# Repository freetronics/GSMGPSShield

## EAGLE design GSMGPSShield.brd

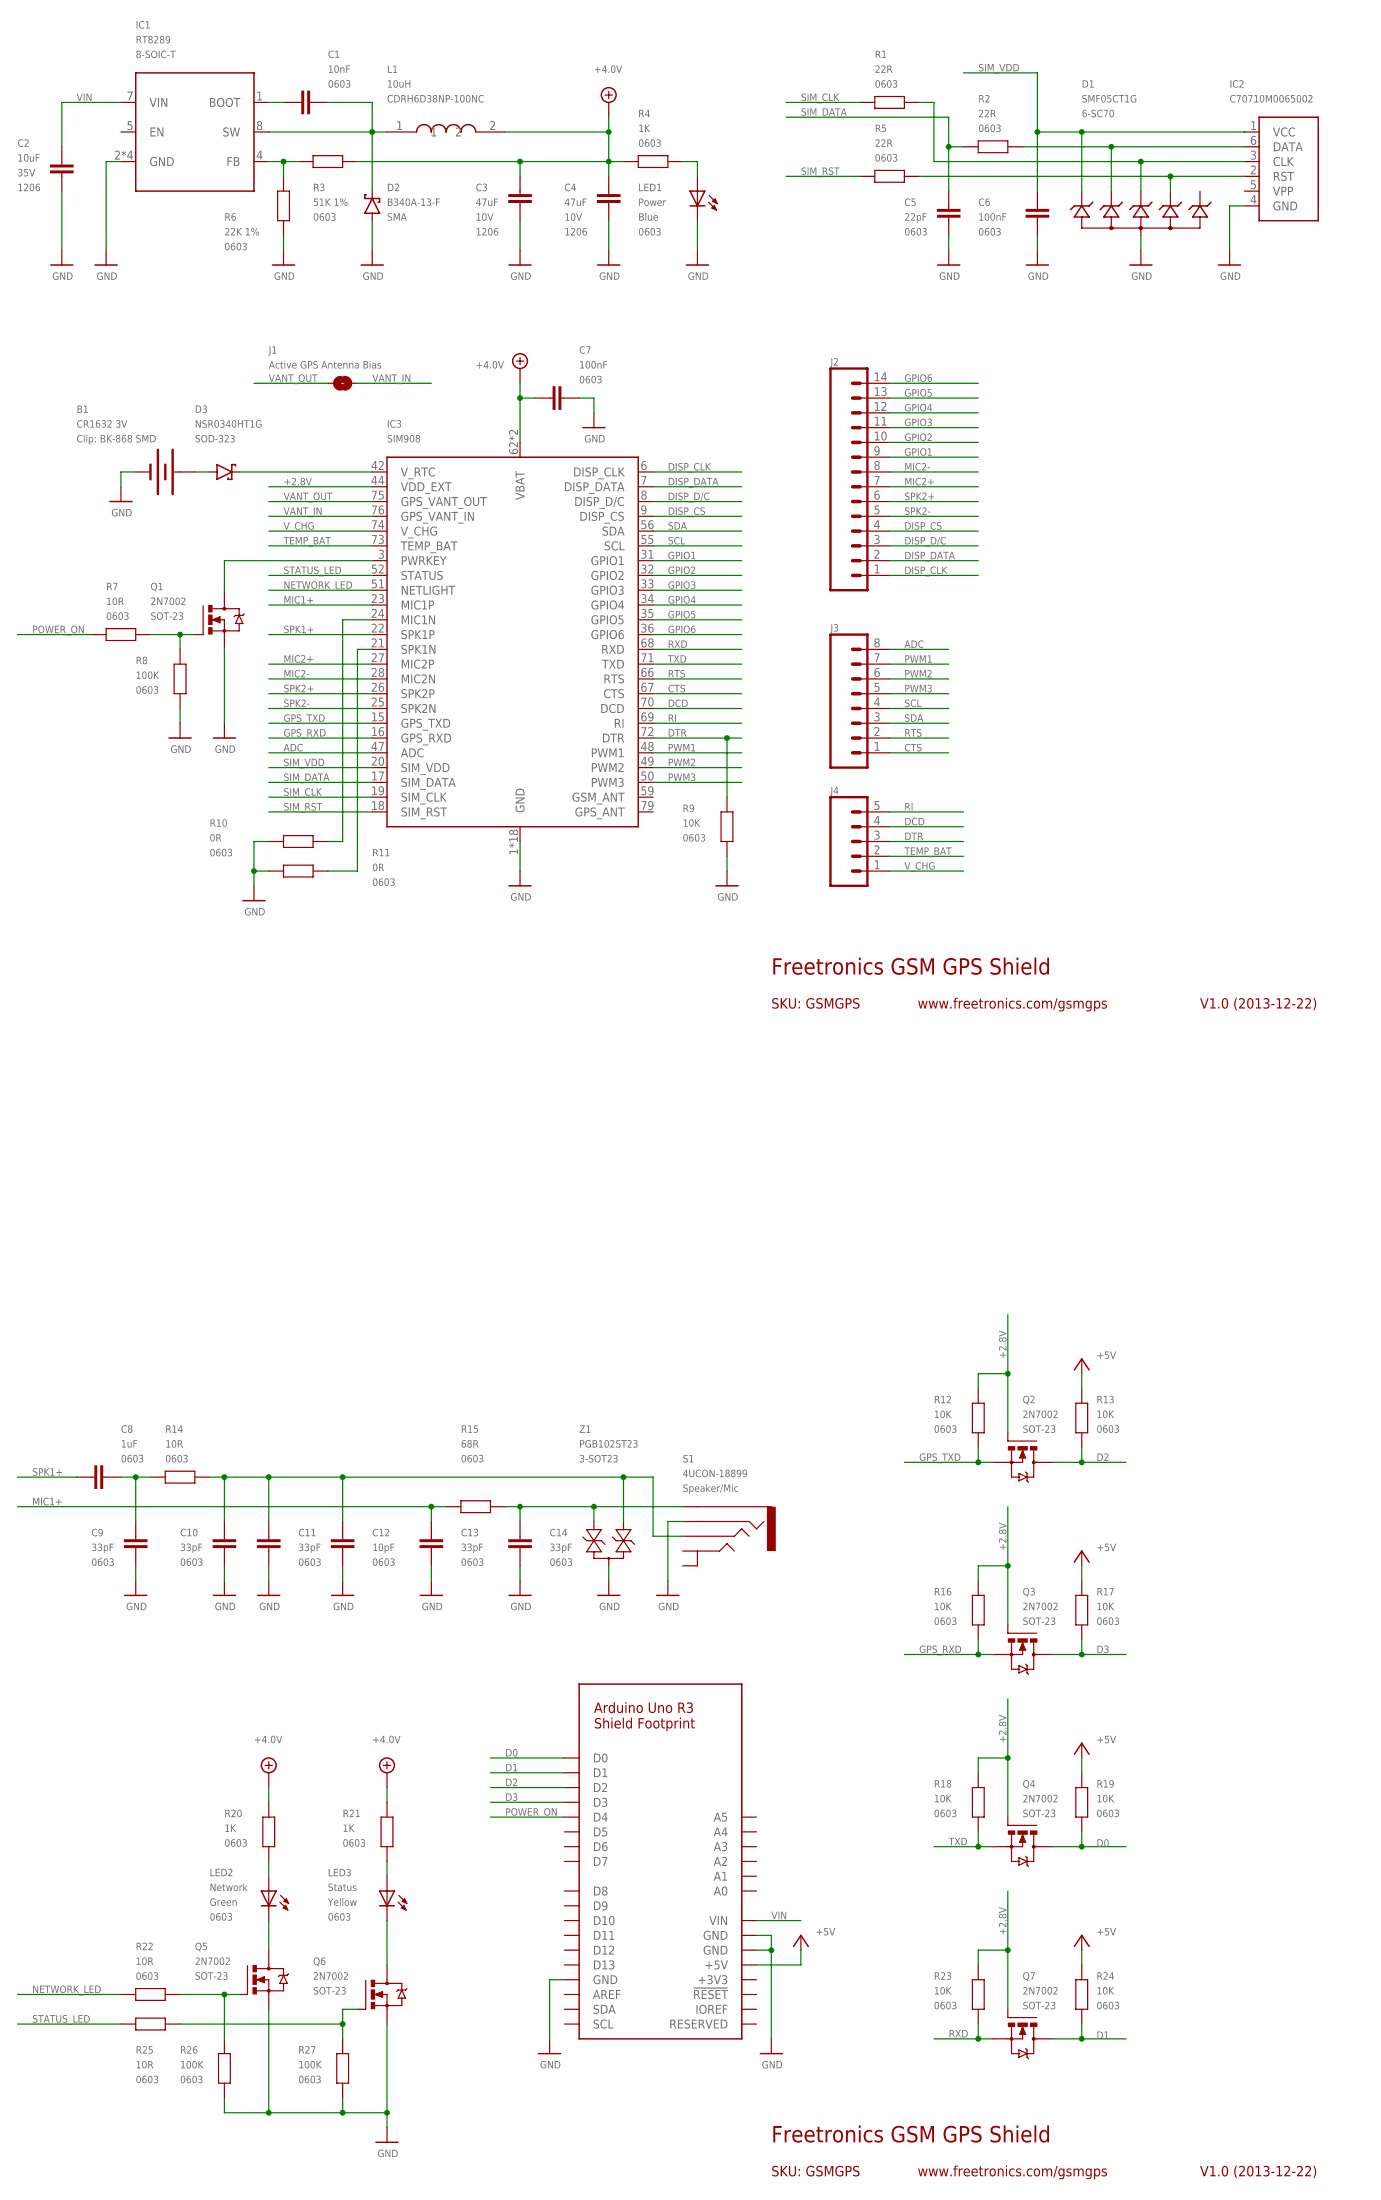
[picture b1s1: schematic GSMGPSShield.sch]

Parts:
B1: CR1632 3V; BATCON_16MM
C1: 10nF; 0603
C2: 10uF; C1206; VOLTAGE 35V
C3, C4: 47uF; C1206; VOLTAGE 10V
C5: 22pF; 0603
C6, C7: 100nF; 0603
C8: 1uF; 0603
C9, C10, C11, C13, C14: 33pF; 0603
C12: 10pF; 0603
D1: SMF05CT1G; SC70-6
D2: B340A-13-F; SMA
D3: NSR0340HT1G; SOD-323
IC1: RT8289; SO08T
IC2: C70710M0065002
IC3: SIM908
J1: Active GPS Antenna Bias; SJ
J2: M14; 1X14
J3: M08STD; 1X08
J4: M05PTH; 1X05
J5: ARDUINO-SHIELD_R3_NOISP
L1: 10uH; CDRH
LED1: Power; LED-0603
LED2: Network; LED-0603
LED3: Status; LED-0603
Q1, Q2, Q3, Q4, Q5, Q6, Q7: 2N7002; SOT23-3
R1, R2, R5: 22R; 0603
R3: 51K 1%; 0603
R4, R20, R21: 1K; 0603
R6: 22K 1%; 0603
R7, R14, R22, R25: 10R; 0603
R8, R26, R27: 100K; 0603
R9, R12, R13, R16, R17, R18, R19, R23, R24: 10K; 0603
R10, R11: 0R; 0603
R15: 68R; 0603
S1: 4UCON-18899
Z1: PGB102ST23; SOT23-3

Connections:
+2.8V: IC3.44 (VDD_EXT), Q2.1 (G), Q3.1 (G), Q4.1 (G), Q7.1 (G), R12.1, R16.1, R18.1, R23.1
+3V3: J5.3V3 (+3V3)
+4.0V: C3.1, C4.1, C7.2, IC3.62 (VBAT), IC3.63 (VBAT), L1.2, R3.1, R4.1, R20.1, R21.1
+5V: J5.+5V, R13.1, R17.1, R19.1, R24.1
ADC: IC3.47 (ADC), J3.8
CTS: IC3.67 (CTS), J3.1
D0: J5.D0, Q4.3 (D), R19.2
D1: J5.D1, Q7.3 (D), R24.2
D2: J5.D2, Q2.3 (D), R13.2
D3: J5.D3, Q3.3 (D), R17.2
DCD: IC3.70 (DCD), J4.4
DISP_CLK: IC3.6 (DISP_CLK), J2.1
DISP_CS: IC3.9 (DISP_CS), J2.4
DISP_D/C: IC3.8 (DISP_D/C), J2.3
DISP_DATA: IC3.7 (DISP_DATA), J2.2
DTR: IC3.72 (DTR), J4.3, R9.1
GND: B1.GND (-), C2.2, C3.2, C4.2, C5.1, C6.1, C7.1, C9.1, C10.1, C11.1, C12.1, C13.1, C14.1, D1.2 (A2), D2.A, IC1.2 (GND), IC1.3 (GND), IC1.6 (GND), IC1.PAD (GND), IC2.4 (GND), IC3.1 (GND), IC3.2 (GND), IC3.5 (GND), IC3.10 (GND), IC3.14 (GND), IC3.37 (GND), IC3.40 (GND), IC3.41 (GND), IC3.43 (GND), IC3.57 (GND), IC3.58 (GND), IC3.60 (GND), IC3.61 (GND), IC3.64 (GND), IC3.65 (GND), IC3.77 (GND), IC3.78 (GND), IC3.80 (GND), J5.GND, J5.GND@0 (GND), J5.GND@1 (GND), LED1.C, Q1.2 (S), Q5.2 (S), Q6.2 (S), R6.1, R8.1, R9.2, R10.2, R11.2, R26.1, R27.1, S1.4, Z1.3
GPIO1: IC3.31 (GPIO1), J2.9
GPIO2: IC3.32 (GPIO2), J2.10
GPIO3: IC3.33 (GPIO3), J2.11
GPIO4: IC3.34 (GPIO4), J2.12
GPIO5: IC3.35 (GPIO5), J2.13
GPIO6: IC3.36 (GPIO6), J2.14
GPS_RXD: IC3.16 (GPS_RXD), Q3.2 (S), R16.2
GPS_TXD: IC3.15 (GPS_TXD), Q2.2 (S), R12.2
MIC1+: C13.2, IC3.23 (MIC1P), R15.1
MIC2+: IC3.27 (MIC2P), J2.7
MIC2-: IC3.28 (MIC2N), J2.8
unnamed: LED1.A, R4.2
unnamed: LED2.C, Q5.3 (D)
unnamed: LED3.C, Q6.3 (D)
unnamed: Q5.1 (G), R22.1, R26.2
unnamed: Q6.1 (G), R25.1, R27.2
unnamed: D3.K, IC3.42 (V_RTC)
unnamed: IC3.3 (PWRKEY), Q1.3 (D)
unnamed: B1.PWR@1 (+), D3.A
unnamed: IC3.21 (SPK1N), R11.1
unnamed: IC3.24 (MIC1N), R10.1
unnamed: D1.5 (K5), IC2.2 (RST), R5.1
unnamed: D1.4 (K4), IC2.3 (CLK), R1.1
unnamed: D1.3 (K3), IC2.6 (DATA), R2.1
unnamed: C14.2, R15.2, S1.1, Z1.2
unnamed: C10.2, C11.2, C12.2, R14.2, S1.3, Z1.1
unnamed: C8.1, C9.2, R14.1
unnamed: Q1.1 (G), R7.1, R8.2
unnamed: LED3.A, R21.2
unnamed: LED2.A, R20.2
unnamed: C1.1, D2.K, IC1.8 (SW), L1.1
unnamed: IC1.4 (FB), R3.2, R6.2
unnamed: C1.2, IC1.1 (BOOT)
NETWORK_LED: IC3.51 (NETLIGHT), R22.2
POWER_ON: J5.D4, R7.2
PWM1: IC3.48 (PWM1), J3.7
PWM2: IC3.49 (PWM2), J3.6
PWM3: IC3.50 (PWM3), J3.5
RI: IC3.69 (RI), J4.5
RTS: IC3.66 (RTS), J3.2
RXD: IC3.68 (RXD), Q7.2 (S), R23.2
SCL: IC3.55 (SCL), J3.4
SDA: IC3.56 (SDA), J3.3
SIM_CLK: IC3.19 (SIM_CLK), R1.2
SIM_DATA: C5.2, IC3.17 (SIM_DATA), R2.2
SIM_RST: IC3.18 (SIM_RST), R5.2
SIM_VDD: C6.2, D1.1 (K1), IC2.1 (VCC), IC3.20 (SIM_VDD)
SPK1+: C8.2, IC3.22 (SPK1P)
SPK2+: IC3.26 (SPK2P), J2.6
SPK2-: IC3.25 (SPK2N), J2.5
STATUS_LED: IC3.52 (STATUS), R25.2
TEMP_BAT: IC3.73 (TEMP_BAT), J4.2
TXD: IC3.71 (TXD), Q4.2 (S), R18.2
VANT_IN: IC3.76 (GPS_VANT_IN), J1.2
VANT_OUT: IC3.75 (GPS_VANT_OUT), J1.1
VIN: C2.1, IC1.7 (VIN), J5.VIN
V_CHG: IC3.74 (V_CHG), J4.1

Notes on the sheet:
Freetronics GSM GPS Shield
V1.0 (2013-12-22)
www.freetronics.com/gsmgps
SKU: GSMGPS

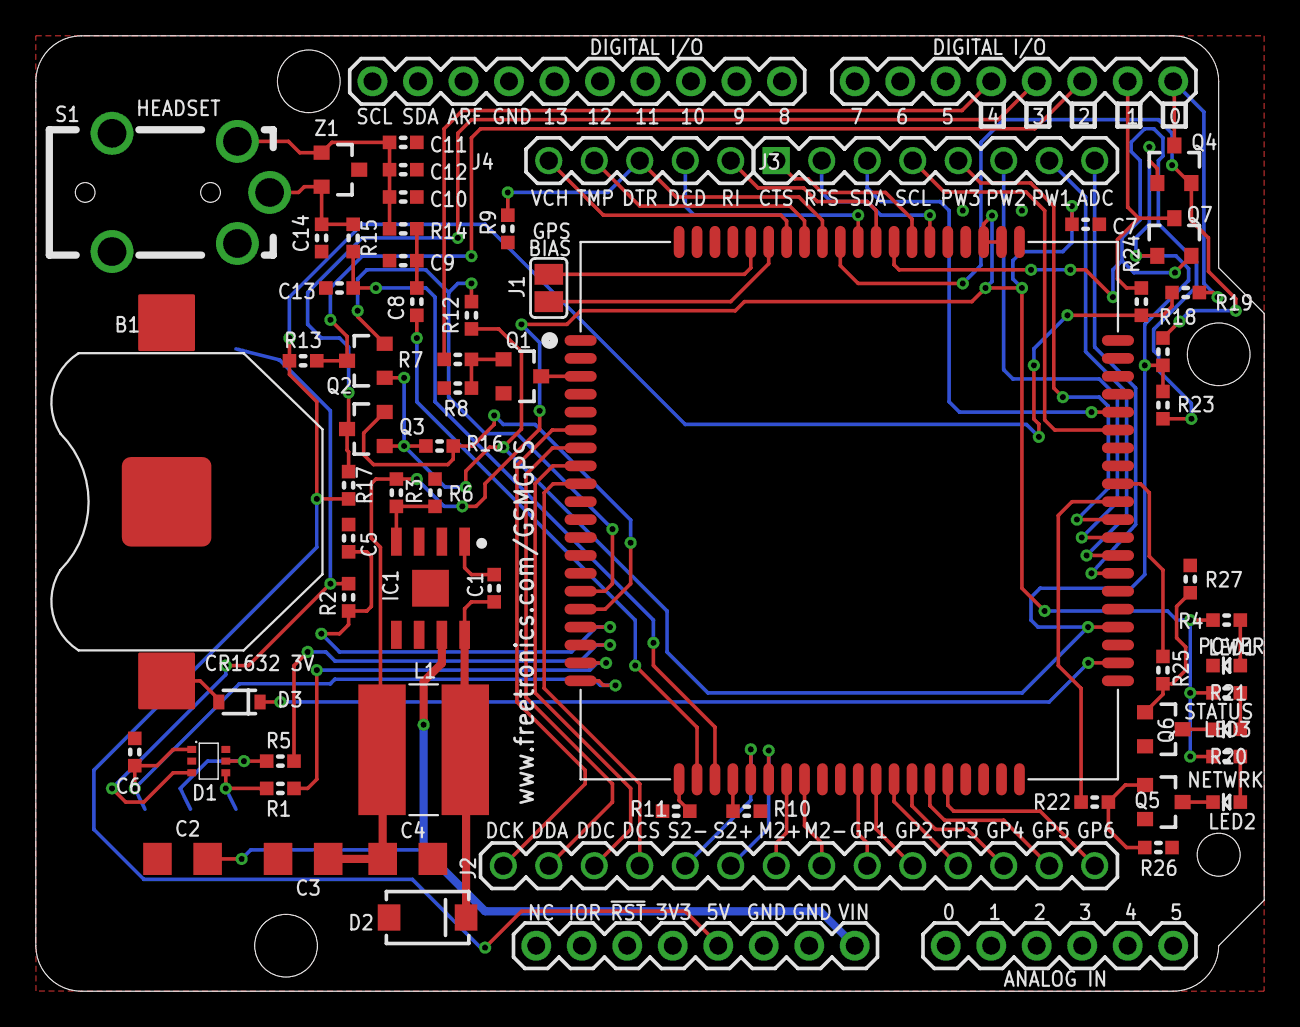
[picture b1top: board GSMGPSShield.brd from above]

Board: 2 copper layers, 68.6 x 53.3 mm, 66 parts (1 on the bottom side), 73 nets.

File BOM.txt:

B1	Memory Protection Devices BK-868 SMD CR1632 coin cell holder (Digi-Key BK-868-ND)
NOTE: A CR1632 3V lithium coin cell also needs to be supplied and mounted in the socket.

S1	4UCON 18899 4-pole audio jack, same as Freetronics ArduPhone
Z1	Littelfuse PGB102ST23WR dual TVS diode, 3-SOT23 package. (Digi-Key F2596CT-ND)

IC3	SIMCom SIM908 GPRS/GPS Module

NOTE: Antenna pigtails with appropriate RF connectors are required to connect to both the GSM and GPS antenna ports on the SIM908 module.

L1	Sumida CDRH6D38NP-100NC 10uH SMD inductor (Digi-Key 308-1541-1-ND) - same footprint as EtherMega inductor

IC1	Richtek RT8289GSP buck converter, 8-SOIC SMD with exposed pad (Digi-Key 1028-1046-1-ND)
IC2	SIM card socket, Amphenol "C707 10M0065 002" 6-pin SIM socket (Digi-Key 361-1020-1-ND)

NOTE: User also needs to supply SIM card, of course.

D1	SMF05CT1G 5-way ESD supressor array, SC70-6 package (Digi-Key SMF05CT1GOSCT-ND)
D2	B340A-13-F schottky diode, SMA package (Digi-Key B340A-FDICT-ND)
D3	NSR0340HT1G schottky diode, SOD323 package (Digi-Key NSR0340HT1GOSCT-ND)

J5	Arduino Shield Headers (2 x 8-pin, 1 x 10-pin, 1 x 6-pin) - placement optional
J2	14-pin 0.1" pin header (NOT PLACED)
J3	8-pin 0.1" pin header (NOT PLACED)

LED1	Blue LED, 0603 SMD
LED2	Green LED, 0603 SMD
LED3	Yellow LED, 0603 SMD

Q1	2N7002 3-SOT23
Q2	2N7002 3-SOT23
Q3	2N7002 3-SOT23
Q4	2N7002 3-SOT23
Q5	2N7002 3-SOT23
Q6	2N7002 3-SOT23
Q7	2N7002 3-SOT23

R1	22R 0603 SMD
R2	22R 0603 SMD
R3	51k 1% 0603 SMD
R4	1k 0603 SMD
R5	22R 0603 SMD
R6	22k 1% 0603 SMD
R7	10R 0603 SMD
R8	100k 0603 SMD
R9	10k 0603 SMD
R10	0R 0603 SMD
R11	0R 0603 SMD
R12	10k 0603 SMD
R13	10k 0603 SMD
R14	10R 0603 SMD
R15	68R 0603 SMD
R16	10k 0603 SMD
R17	10k 0603 SMD
R18	10k 0603 SMD
R19	10k 0603 SMD
R20	1k 0603 SMD
R21	1k 0603 SMD
R22	10R 0603 SMD
R23	10k 0603 SMD
R24	10k 0603 SMD
R25	10R 0603 SMD
R26	100k 0603 SMD
R27	100k 0603 SMD

C1	10nF 50V 0603 SMD ceramic
C2	10uF 35V 1206 SMD ceramic
C3	47uF 10V 1206 SMD ceramic
C4	47uF 10V 1206 SMD ceramic

NOTE: Do not reduce specified voltage ratings for C2, C3, C4

C5	22pF 50V 0603 SMD ceramic
C6	100nF 50V 0603 SMD ceramic
C7	100nF 50V 0603 SMD ceramic
C8	1uF 50V 0603 SMD ceramic
C9	33pF 50V 0603 SMD ceramic
C10	33pF 50V 0603 SMD ceramic
C11	33pF 50V 0603 SMD ceramic
C12	10pF 50V 0603 SMD ceramic
C13	33pF 50V 0603 SMD ceramic
C14	33pF 50V 0603 SMD ceramic

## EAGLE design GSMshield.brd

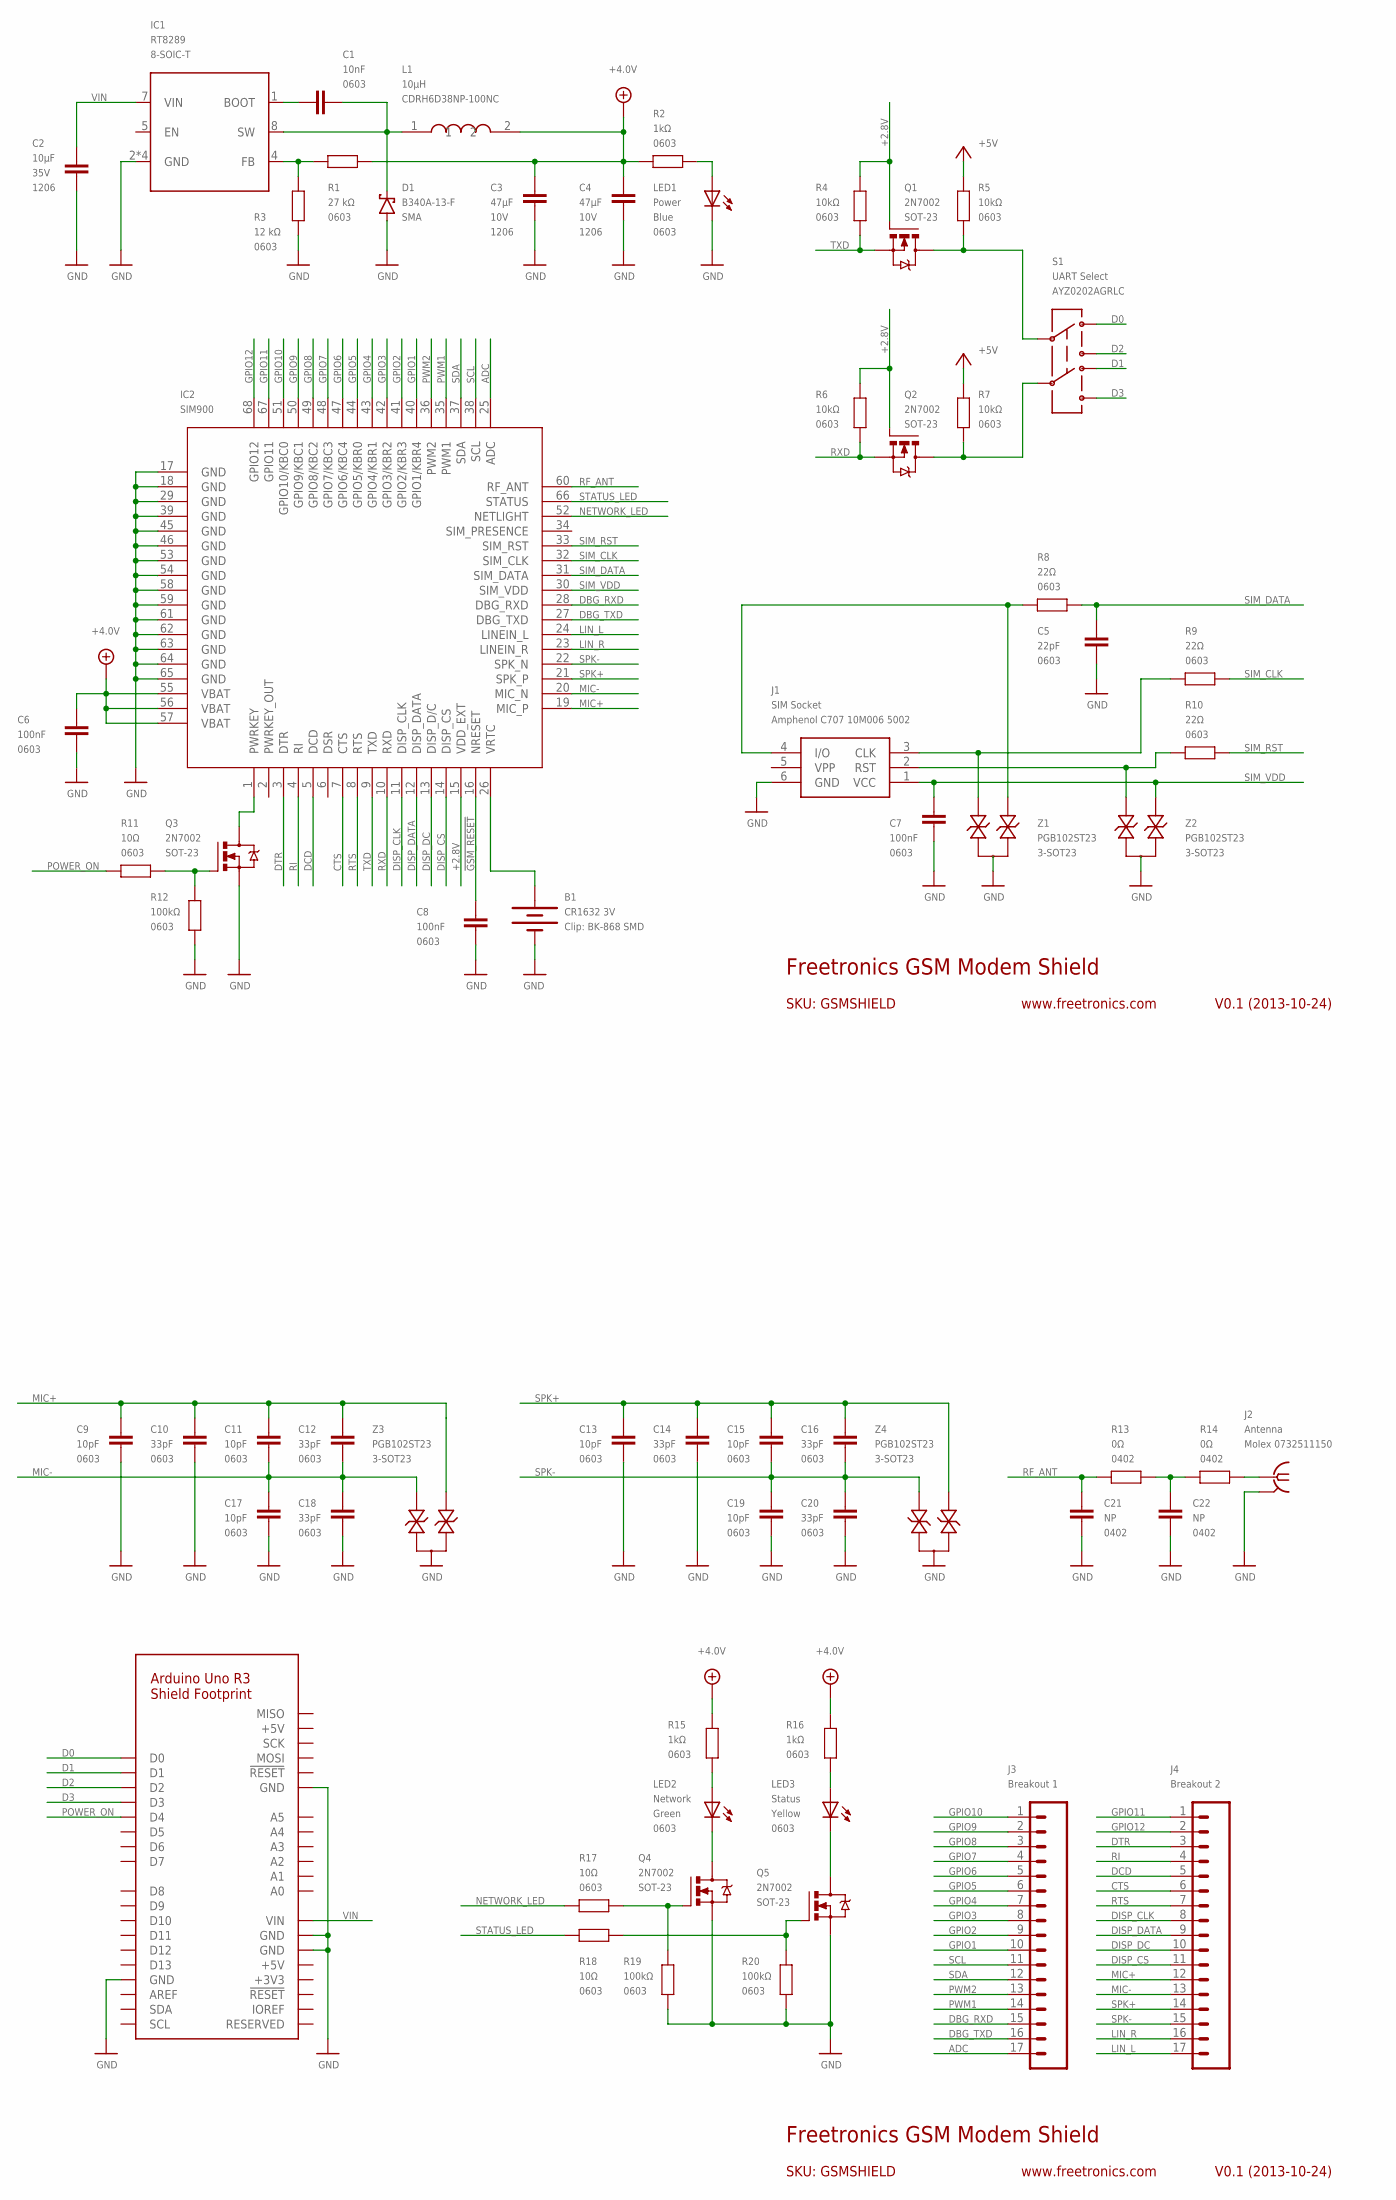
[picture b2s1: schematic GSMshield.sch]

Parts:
B1: CR1632 3V; BATCON_16MM
C1: 10nF; 0603
C2: 10µF; C1206; VOLTAGE 35V
C3, C4: 47µF; C1206; VOLTAGE 10V
C5: 22pF; 0603
C6, C7, C8: 100nF; 0603
C9, C11, C13, C15, C17, C19: 10pF; 0603
C10, C12, C14, C16, C18, C20: 33pF; 0603
C21, C22: NP; C0402
D1: B340A-13-F; SMA
IC1: RT8289; SO08T
IC2: SIM900
J1: SIM Socket; SIMHOLDER3
J2: Antenna; J502-ND-142-0701-881/886
J3: Breakout 1; 1X17
J4: Breakout 2; 1X17
J5: ARDUINO-SHIELD_R3
L1: 10µH; CDRH
LED1: Power; LED-0603
LED2: Network; LED-0603
LED3: Status; LED-0603
Q1, Q2, Q3, Q4, Q5: 2N7002; SOT23-3
R1: 27 kΩ; 0603
R2, R15, R16: 1kΩ; 0603
R3: 12 kΩ; 0603
R4, R5, R6, R7: 10kΩ; 0603
R8, R9, R10: 22Ω; 0603
R11, R17, R18: 10Ω; 0603
R12, R19, R20: 100kΩ; 0603
R13, R14: 0Ω; C0402
S1: UART Select; AYZ0202
Z1, Z2, Z3, Z4: PGB102ST23; SOT23-3

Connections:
!GSM_RESET: C8.2, IC2.16 (NRESET)
+2.8V: IC2.15 (VDD_EXT), Q1.1 (G), Q2.1 (G), R4.1, R6.1
+3V3: J5.3V3 (+3V3)
+4.0V: C3.1, C4.1, C6.2, IC2.55 (VBAT), IC2.56 (VBAT), IC2.57 (VBAT), L1.2, R1.1, R2.1, R15.1, R16.1
+5V: J5.+5V, R5.1, R7.1
ADC: IC2.25 (ADC), J3.17
CTS: IC2.7 (CTS), J4.6
D0: J5.D0, S1.1
D1: J5.D1, S1.4
D2: J5.D2, S1.3
D3: J5.D3, S1.6
DBG_RXD: IC2.28 (DBG_RXD), J3.15
DBG_TXD: IC2.27 (DBG_TXD), J3.16
DCD: IC2.5 (DCD), J4.5
DISP_CLK: IC2.11 (DISP_CLK), J4.8
DISP_CS: IC2.14 (DISP_CS), J4.11
DISP_DATA: IC2.12 (DISP_DATA), J4.9
DISP_DC: IC2.13 (DISP_D/C), J4.10
DTR: IC2.3 (DTR), J4.3
GND: B1.GND (-), C2.2, C3.2, C4.2, C5.1, C6.1, C7.1, C8.1, C9.1, C10.1, C13.1, C14.1, C17.1, C18.1, C19.1, C20.1, C21.1, C22.1, D1.A, IC1.2 (GND), IC1.3 (GND), IC1.6 (GND), IC1.PAD (GND), IC2.17 (GND), IC2.18 (GND), IC2.29 (GND), IC2.39 (GND), IC2.45 (GND), IC2.46 (GND), IC2.53 (GND), IC2.54 (GND), IC2.58 (GND), IC2.59 (GND), IC2.61 (GND), IC2.62 (GND), IC2.63 (GND), IC2.64 (GND), IC2.65 (GND), J1.6 (GND), J2.G@1 (GND), J2.G@2 (GND), J2.G@3 (GND), J2.G@4 (GND), J5.GND, J5.GND@0 (GND), J5.GND@1 (GND), J5.GND@2 (GND), LED1.C, Q3.2 (S), Q4.2 (S), Q5.2 (S), R3.1, R12.1, R19.1, R20.1, Z1.3, Z2.3, Z3.3, Z4.3
GPIO1: IC2.40 (GPIO1/KBR4), J3.10
GPIO2: IC2.41 (GPIO2/KBR3), J3.9
GPIO3: IC2.42 (GPIO3/KBR2), J3.8
GPIO4: IC2.43 (GPIO4/KBR1), J3.7
GPIO5: IC2.44 (GPIO5/KBR0), J3.6
GPIO6: IC2.47 (GPIO6/KBC4), J3.5
GPIO7: IC2.48 (GPIO7/KBC3), J3.4
GPIO8: IC2.49 (GPIO8/KBC2), J3.3
GPIO9: IC2.50 (GPIO9/KBC1), J3.2
GPIO10: IC2.51 (GPIO10/KBC0), J3.1
GPIO11: IC2.67 (GPIO11), J4.1
GPIO12: IC2.68 (GPIO12), J4.2
LIN_L: IC2.24 (LINEIN_L), J4.17
LIN_R: IC2.23 (LINEIN_R), J4.16
MIC+: C9.2, C10.2, C11.2, C12.2, IC2.19 (MIC_P), J4.12, Z3.2
MIC-: C11.1, C12.1, C17.2, C18.2, IC2.20 (MIC_N), J4.13, Z3.1
unnamed: LED1.A, R2.2
unnamed: LED2.C, Q4.3 (D)
unnamed: LED3.C, Q5.3 (D)
unnamed: Q4.1 (G), R17.1, R19.2
unnamed: Q5.1 (G), R18.1, R20.2
unnamed: B1.PWR@1 (+), IC2.26 (VRTC)
unnamed: J1.2 (RST), R10.2, Z2.1
unnamed: J1.3 (CLK), R9.2, Z1.1
unnamed: J1.4 (I/O), R8.2, Z1.2
unnamed: IC2.1 (PWRKEY), Q3.3 (D)
unnamed: Q3.1 (G), R11.1, R12.2
unnamed: C22.2, R13.2, R14.1
unnamed: J2.1, R14.2
unnamed: LED3.A, R16.2
unnamed: LED2.A, R15.2
unnamed: C1.1, D1.K, IC1.8 (SW), L1.1
unnamed: IC1.4 (FB), R1.2, R3.2
unnamed: C1.2, IC1.1 (BOOT)
NETWORK_LED: IC2.52 (NETLIGHT), R17.2
POWER_ON: J5.D4, R11.2
PWM1: IC2.35 (PWM1), J3.14
PWM2: IC2.36 (PWM2), J3.13
RF_ANT: C21.2, IC2.60 (RF_ANT), R13.1
RI: IC2.4 (RI), J4.4
RTS: IC2.8 (RTS), J4.7
RXD: IC2.10 (RXD), Q2.2 (S), R6.2
RXD_5V: Q2.3 (D), R7.2, S1.5
SCL: IC2.38 (SCL), J3.11
SDA: IC2.37 (SDA), J3.12
SIM_CLK: IC2.32 (SIM_CLK), R9.1
SIM_DATA: C5.2, IC2.31 (SIM_DATA), R8.1
SIM_RST: IC2.33 (SIM_RST), R10.1
SIM_VDD: C7.2, IC2.30 (SIM_VDD), J1.1 (VCC), Z2.2
SPK+: C13.2, C14.2, C15.2, C16.2, IC2.21 (SPK_P), J4.14, Z4.1
SPK-: C15.1, C16.1, C19.2, C20.2, IC2.22 (SPK_N), J4.15, Z4.2
STATUS_LED: IC2.66 (STATUS), R18.2
TXD: IC2.9 (TXD), Q1.2 (S), R4.2
TXD_5V: Q1.3 (D), R5.2, S1.2
VIN: C2.1, IC1.7 (VIN), J5.VIN

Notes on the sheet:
Freetronics GSM Modem Shield
V0.1 (2013-10-24)
www.freetronics.com
SKU: GSMSHIELD

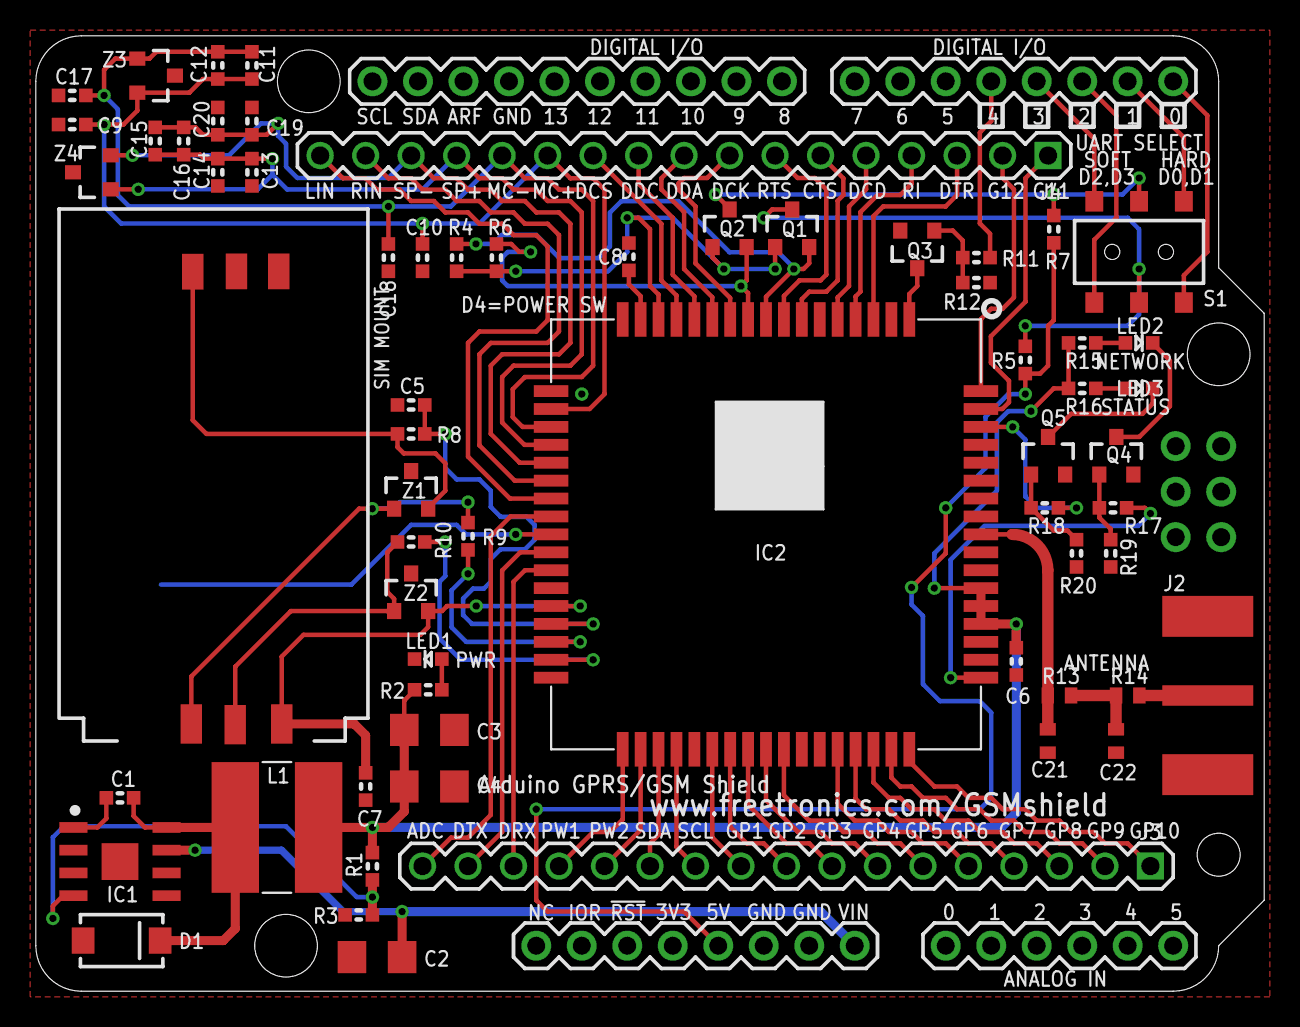
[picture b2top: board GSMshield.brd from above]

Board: 2 copper layers, 68.6 x 53.3 mm, 65 parts (1 on the bottom side), 74 nets.

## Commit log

2013-11-01 tweaked readme
2013-12-05 Changed all fonts to vector Increased VIA size Added version number and license to overlay Added chip orientation markers in tdocu layer Repositioned designators
2013-12-13 Renamed files to convert to SIM908
2013-12-27 changed to SIM908 module, first finished draft
2014-01-22 Replaced Greek characters with Latin equivalents
2014-01-22 Relocated project close to 0,0 origin. Couldn't get it quite right
2014-01-23 Replaced level shifter FETs with RJU003N03
2014-01-23 Fixed footprint for headphone socket Changed pin assignments to D2-D6 to clear D0/D1 UART for programming Added ICSP header for pass-through Replaced level shifter FETs with RJU003N03 Added orientati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

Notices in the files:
GSMGPSShield.brd:
Copyright 2013 Freetronics Pty Ltd
Released under the terms of the
TAPR Open Hardware License
